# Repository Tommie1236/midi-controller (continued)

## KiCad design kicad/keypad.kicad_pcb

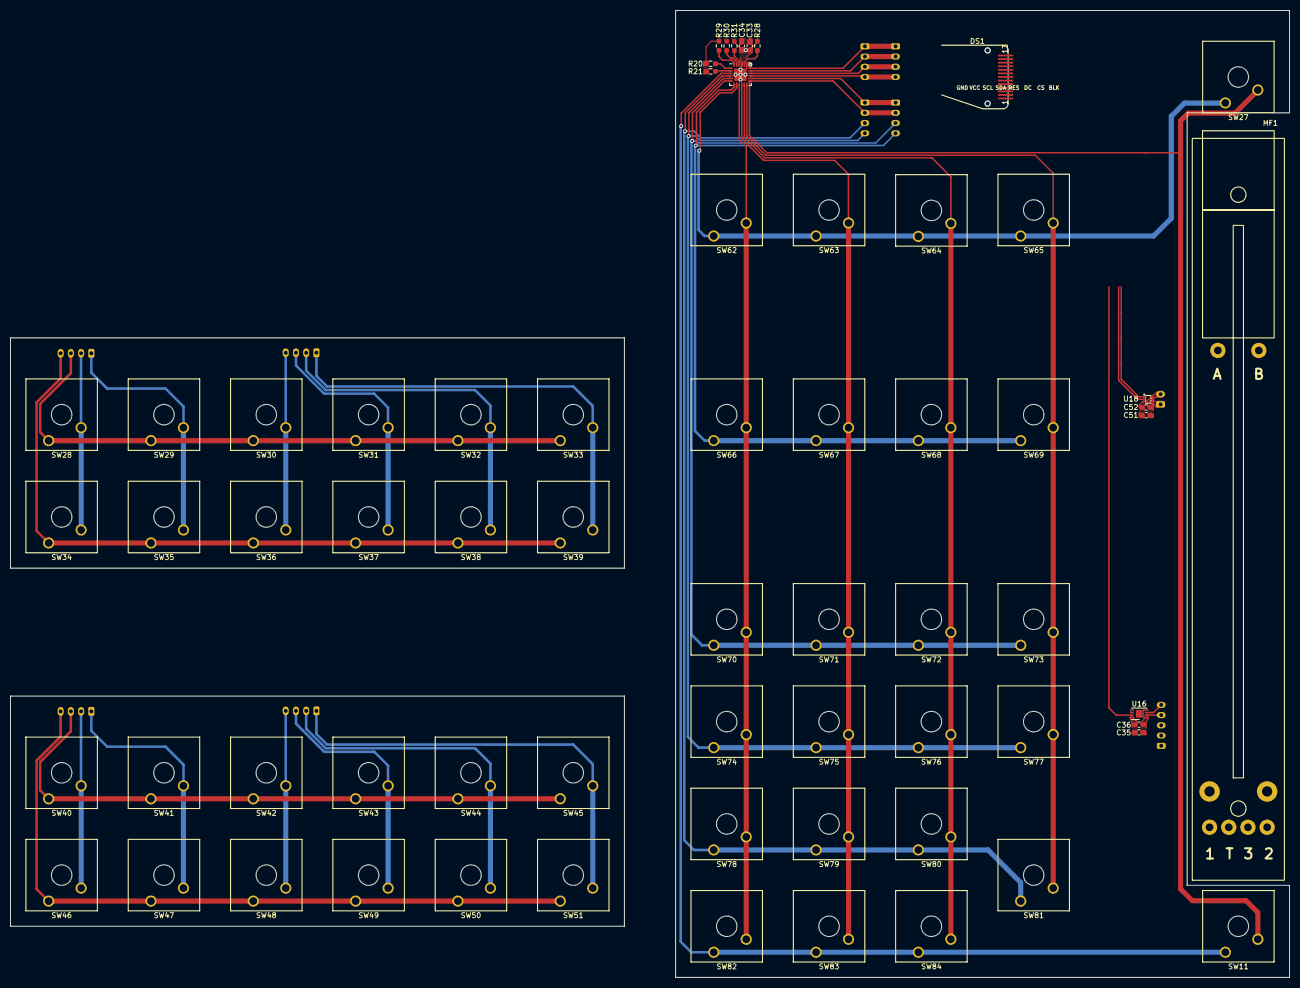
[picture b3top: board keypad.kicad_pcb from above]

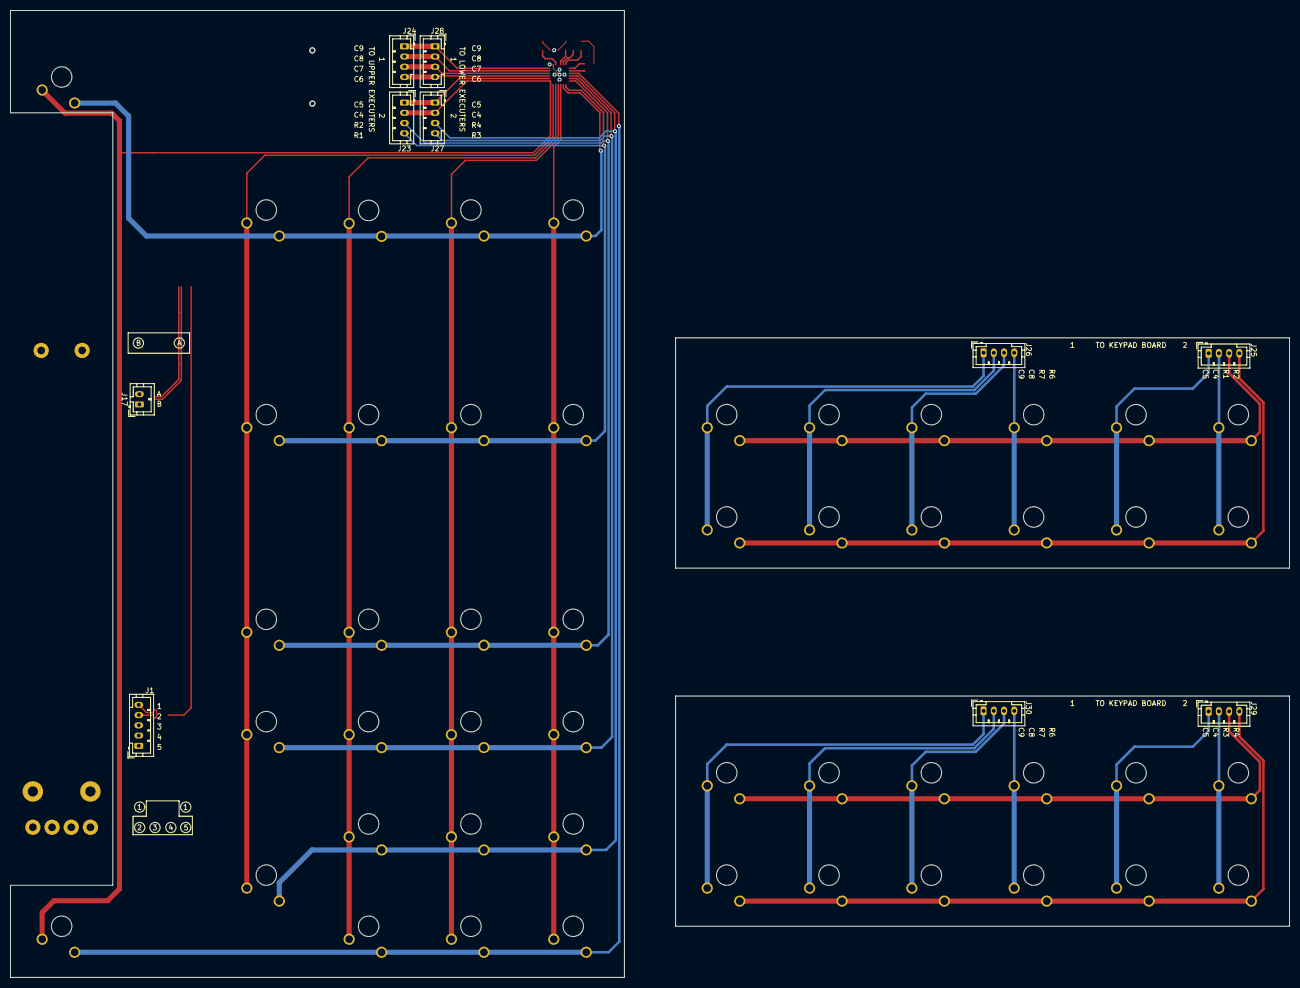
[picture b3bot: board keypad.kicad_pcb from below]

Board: 2 copper layers, 250.0 x 189.0 mm, 76 parts (10 on the bottom side), 45 nets.

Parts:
C33, C35: 1u; C_0603_1608Metric_Pad1.08x0.95mm_HandSolder
C34, C36, C52: 100n; C_0603_1608Metric_Pad1.08x0.95mm_HandSolder
C51: 100u; C_0603_1608Metric_Pad1.08x0.95mm_HandSolder
DS1: 1.05" 130*240 spi screen; 1.05' 120x240 spi screen
J1: Conn_01x05_Socket; JST_PH_B5B-PH-K_1x05_P2.00mm_Vertical
J17: Conn_01x02_Socket; JST_PH_B2B-PH-K_1x02_P2.00mm_Vertical
J23, J24, J25, J26, J27, J28, J29, J30: Conn_01x04_Socket; JST_PH_B4B-PH-K_1x04_P2.00mm_Vertical
MF1: RSA0N11M9A0J
R20, R21: 10K; R_0603_1608Metric_Pad0.98x0.95mm_HandSolder
R28, R29, R30, R31: 4K7; R_0603_1608Metric_Pad0.98x0.95mm_HandSolder
SW11, SW27, SW28, SW29, SW30, SW31, SW32, SW33, SW34, SW35, SW36, SW37, SW38, SW39, SW40, SW41, SW42, SW43, SW44, SW45, SW46, SW47, SW48, SW49, SW50, SW51, SW62, SW63, SW64, SW65, SW66, SW67, SW68, SW69, SW70, SW71, SW72, SW73, SW74, SW75, SW76, SW77, SW78, SW79, SW80, SW82, SW83, SW84: SW_SPST; SW_Cherry_MX_1.00u_Plate
SW81: SW_SPST; SW_Cherry_MX_2.00u_Vertical_Plate
U7: TCA8418; WQFN-24-1EP_4x4mm_P0.5mm_EP2.45x2.45mm
U16: MTCH102; DFN-8-1EP_3x2mm_P0.5mm_EP1.3x1.5mm
U18: DRV8210; SOT-6

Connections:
+3V3: C33.1, C34.1, C35.1, C36.1, DS1.2 (VCC), J1.2, R20.1, R21.1, R28.1, R29.1, R30.1, R31.1, U7.21 (VCC), U16.1 (VCC), U16.4 (LPMS)
/INT-KEYP: R29.2, U7.24 (~INT)
/RST-KEYP: R28.2, U7.20 (~RESET)
/SCL-KEYP: R30.2, U7.23 (SCL)
/SDA-KEYP: R31.2, U7.22 (SDA)
COL0: SW62.2 (B), SW66.2 (B), SW70.2 (B), SW74.2 (B), SW78.2 (B), SW82.2 (B), U7.9 (COL0)
COL1: SW63.2 (B), SW67.2 (B), SW71.2 (B), SW75.2 (B), SW79.2 (B), SW83.2 (B), U7.10 (COL1)
COL2: SW64.2 (B), SW68.2 (B), SW72.2 (B), SW76.2 (B), SW80.2 (B), SW84.2 (B), U7.11 (COL2)
COL3: SW65.2 (B), SW69.2 (B), SW73.2 (B), SW77.2 (B), SW81.2 (B), U7.12 (COL3)
COL4: J23.2, J27.2, SW11.2 (B), SW27.2 (B), U7.13 (COL4)
COL5: J23.1, J27.1, U7.14 (COL5)
COL6: J24.4, J28.4, U7.15 (COL6)
COL7: J24.3, J28.3, U7.16 (COL7)
COL8: J24.2, J28.2, U7.17 (COL8)
COL9: J24.1, J28.1, U7.18 (COL9)
GND: C33.2, C34.2, C35.2, C36.2, C51.2, C52.2, DS1.1 (GND), J1.3, U7.19 (GND), U16.8 (GND), U18.3 (GND)
MF-G: J1.5, U16.3 (T1/AG)
MF-T: J1.4, U16.2 (T0)
MFA: J17.1, U18.4 (O2)
MFB: J17.2, U18.6 (O1)
unnamed: R21.2, U7.2 (ROW6)
unnamed: R20.2, U7.1 (ROW7)
ROW0: SW27.1 (A), SW62.1 (A), SW63.1 (A), SW64.1 (A), SW65.1 (A), U7.8 (ROW0)
ROW1: J23.4, SW66.1 (A), SW67.1 (A), SW68.1 (A), SW69.1 (A), U7.7 (ROW1)
ROW2: J23.3, SW70.1 (A), SW71.1 (A), SW72.1 (A), SW73.1 (A), U7.6 (ROW2)
ROW3: J27.4, SW74.1 (A), SW75.1 (A), SW76.1 (A), SW77.1 (A), U7.5 (ROW3)
ROW4: J27.3, SW78.1 (A), SW79.1 (A), SW80.1 (A), SW81.1 (A), U7.4 (ROW4)
ROW5: SW11.1 (A), SW82.1 (A), SW83.1 (A), SW84.1 (A), U7.3 (ROW5)
VFMOT: C51.1, C52.1, U18.5 (MVCC)
exe1-COL4: J25.2, SW28.2 (B), SW34.2 (B)
exe1-COL5: J25.1, SW29.2 (B), SW35.2 (B)
exe1-COL6: J26.4, SW30.2 (B), SW36.2 (B)
exe1-COL7: J26.3, SW31.2 (B), SW37.2 (B)
exe1-COL8: J26.2, SW32.2 (B), SW38.2 (B)
exe1-COL9: J26.1, SW33.2 (B), SW39.2 (B)
exe1-ROW1: J25.3, SW28.1 (A), SW29.1 (A), SW30.1 (A), SW31.1 (A), SW32.1 (A), SW33.1 (A)
exe1-ROW2: J25.4, SW34.1 (A), SW35.1 (A), SW36.1 (A), SW37.1 (A), SW38.1 (A), SW39.1 (A)
exe2-COL4: J29.2, SW40.2 (B), SW46.2 (B)
exe2-COL5: J29.1, SW41.2 (B), SW47.2 (B)
exe2-COL6: J30.4, SW42.2 (B), SW48.2 (B)
exe2-COL7: J30.3, SW43.2 (B), SW49.2 (B)
exe2-COL8: J30.2, SW44.2 (B), SW50.2 (B)
exe2-COL9: J30.1, SW45.2 (B), SW51.2 (B)
exe2-ROW3: J29.3, SW40.1 (A), SW41.1 (A), SW42.1 (A), SW43.1 (A), SW44.1 (A), SW45.1 (A)
exe2-ROW4: J29.4, SW46.1 (A), SW47.1 (A), SW48.1 (A), SW49.1 (A), SW50.1 (A), SW51.1 (A)

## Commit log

2024-07-08 added pico-sdk submodule
2024-07-08 add cpp gitignore
2024-07-08 add files from the amazing thacher/RP2040_SKELETON repository
2024-07-08 added project files so for
2024-07-08 remove picotool as unnessesary
2024-07-08 add gcc-arm-none-eabi
2024-07-08 immediatly exit build.sh if error in compile
2024-07-08 remove mkdir error
2024-07-08 test gh actions fail compile
2024-07-09 remove test compile error
2024-08-02 only upload on no error and print firmware location
2024-08-02 started implementing a different pin strategy for the mcp23s17/rp2040
2024-08-02 added kicad and freecad hardware files to repo
2024-08-02 try fixing submodules
2024-08-02 try again with submodule file;
2024-08-02 submodule file update
2024-08-02 readd pico-sdk submodule
2024-08-02 hopefully fixed pico-sdk submodule
2024-08-02 Created a Readme and added the requirements for this project to it.
2024-08-03 first version of "following fader"
    works but is only sort of smooth at lower voltages and thus lower motor speeds. needs pid later probably. now it is just full speed up or down.
2024-08-03 fixed read_adc result calculation
2024-08-03 remove some debug code
2024-08-03 remove some debug code (2)
2024-08-03 removed stupid *0.5 that had me searching for bugs for half an hour
2024-08-07 remove kicad backups from repo
2024-08-07 some little changes. don't really know what, sorry
2024-08-07 add kicad backups to gitignore
2024-08-07 removed some more unnessesary kicad files
2024-08-07 add unnessesary model files to gitignore
2024-08-07 remove unnesseary model files from repo
2024-08-07 finish optional requirements in readme
2024-08-07 fix missed md linebreaks
2024-08-07 typo
2024-08-07 small readme edit
2024-08-08 moved Pin to its own folder as it is no longer only part of the mcp23s17
    I Know this wont conpile as it has errors that are caused by moving and
    changing the `Pin` implementation. Will be fixed in next commit.
2024-08-21 update kicad files
2024-08-22 small refactors
2024-08-22 add tlc59282 datasheet
    and some other small updates to docs
2024-08-22 add/update some model files
2024-08-25 changed the project structure and fixed cmake (hopefully)
    changed the project to have a separeate rp2040 in each fader wing for control there. so i needed 2 binaries that both used the same libraries for components. and after moving those and (what i though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
2024-08-25 tried to upgrade the build file.
    bash was too hard and python argparse wouldn't do what i wanted. sorry
2024-08-25 split build.sh into 2 files
    hardcoded the files for now as i couldn't get a fancier script to work. (see last commit)
2024-08-25 update action file for the changes of the build scripts
2024-08-25 fix type in build test action
    bulld -> build (ln23)
2024-08-25 tested the tlc59282 with some patterns
2024-08-27 first version of keycap insert.
2024-08-27 forgot to also add stl
2024-08-27 next iteration
2024-08-27 add pca9635 datasheet to docs
2024-08-27 feat(schem): started implementing the rp2040 on each wing
2024-08-27 changed some more of the schematic
2024-08-27 feat(sch): mostly figured uit pinout for rp2040 and some other small edits
2024-08-30 feat(pcb): routing tracks from mcu to pheriperals
2024-09-03 created test stand for faders
    they were annoying to hold in my hands the entire time i need to use them for tests
2024-09-04 split builds into 2 actions
2024-09-04 added action status badges to readme
2024-09-08 chore : remove unnessesary/unfinished py scripts
2024-09-25 continued work on fader pcb and redid all references more logicly
2024-09-25 hopefully make the keycap insert fit into standard mx switches
2024-09-25 added print files from last update
2024-09-25 small updates, add fillet to inside corners and check overall dimentsions
2024-09-25 fits pretty well. decreased stem lenght to 4mm
2024-09-28 update gitignore to ignore freecad backups
2024-09-28 reorderd model files
2024-09-28 add first few keycap models
2024-09-28 update keycap progress file format for better readability
2024-09-28 add user and bank keycap models
2024-09-28 add blackout and bpm keycap
2024-09-28 add arrow (up/down, all directions in one) and bpm
2024-09-28 added executor keycaps
2024-09-28 moved tools to their own directory and updated workflows because of that
2024-09-28 found out that model drawing was far out of date on github so here is current version
2024-09-28 changed to compressed version for drawio render workflow
2024-09-28 add render drawio action badge to readme
2024-09-28 add dummyfile for drawio workflow to overwrite
2024-09-28 try some edits
2024-09-28 cant find why not worky. replaced paths with correct ones and will disable
2024-09-28 Create fader pid control.md
    save url for fader pid control
2024-10-18 Add kicad lock files to .gitignore
2024-10-18 finish updateing all references, add schematic pdf and some more progress
2024-10-19 add some more unnessesary kicad files to gitignore
2024-10-19 some more progress on the fader pcb and small changes to schematic
2024-10-19 comment out drawio render badge, action doesn't work and cant be bothered to fix anytime soon
2024-10-19 test gpg signing
2024-10-20 chose sk6812 mini as led for all the keys, added datasheet
2024-10-20 replaced normal mx footprints to ones that also support hot swap sockets and have leds build in.
    updated schematic and pcb to accomodate this. didn't connect the leds in the footprint yet
2024-10-20 fix kicad cache exclusion in gitignore
2024-10-20 forgot to add updated pdf to last schematic change
2024-10-24 fix(build) : fix a path that i forgot to update after moving the file
2024-10-24 update workflow files for updated build scripts
2024-10-24 updated build scripts to only build one of the binaries
2024-10-24 always touch the main source file so the linker will print the used memory info
2024-10-25 started working on encoder implementation. leds almost finished
2024-10-30 remove some unnessesary files and added 2 new datasheets of the motor faders
2024-10-30 more progress on fader pcb. moved around ls30's to make space for hot swap sockets
2024-10-30 fix (schematic) : add missing power symbol to encoder leds
2024-10-30 feat (schematic) : link tlc59282's and small edits
    not happy with the link from top right to bottom left. TODO: fix that later
2024-10-30 removed some outdated design files
2024-10-30 keep .vscode folder from repo
2025-01-29 pushed unsaved kicad files. don't know what changed
2025-01-29 small fix to build scripts
2025-01-30 completely reworked pin implementation
2025-01-30 deprecated old pin implementation
    i know this doesn't compile. will fix the dependant files shortly
2025-01-31 fixed that there isn't a rp2040 object to work with
    removed al the references to the rp2040 object and assumed that if there isn't a parent object given it is the rp2040
2025-01-31 allow parent objects to be mutable while locking the pointer
    instead of locking the pointer and making the parent object unmutable
